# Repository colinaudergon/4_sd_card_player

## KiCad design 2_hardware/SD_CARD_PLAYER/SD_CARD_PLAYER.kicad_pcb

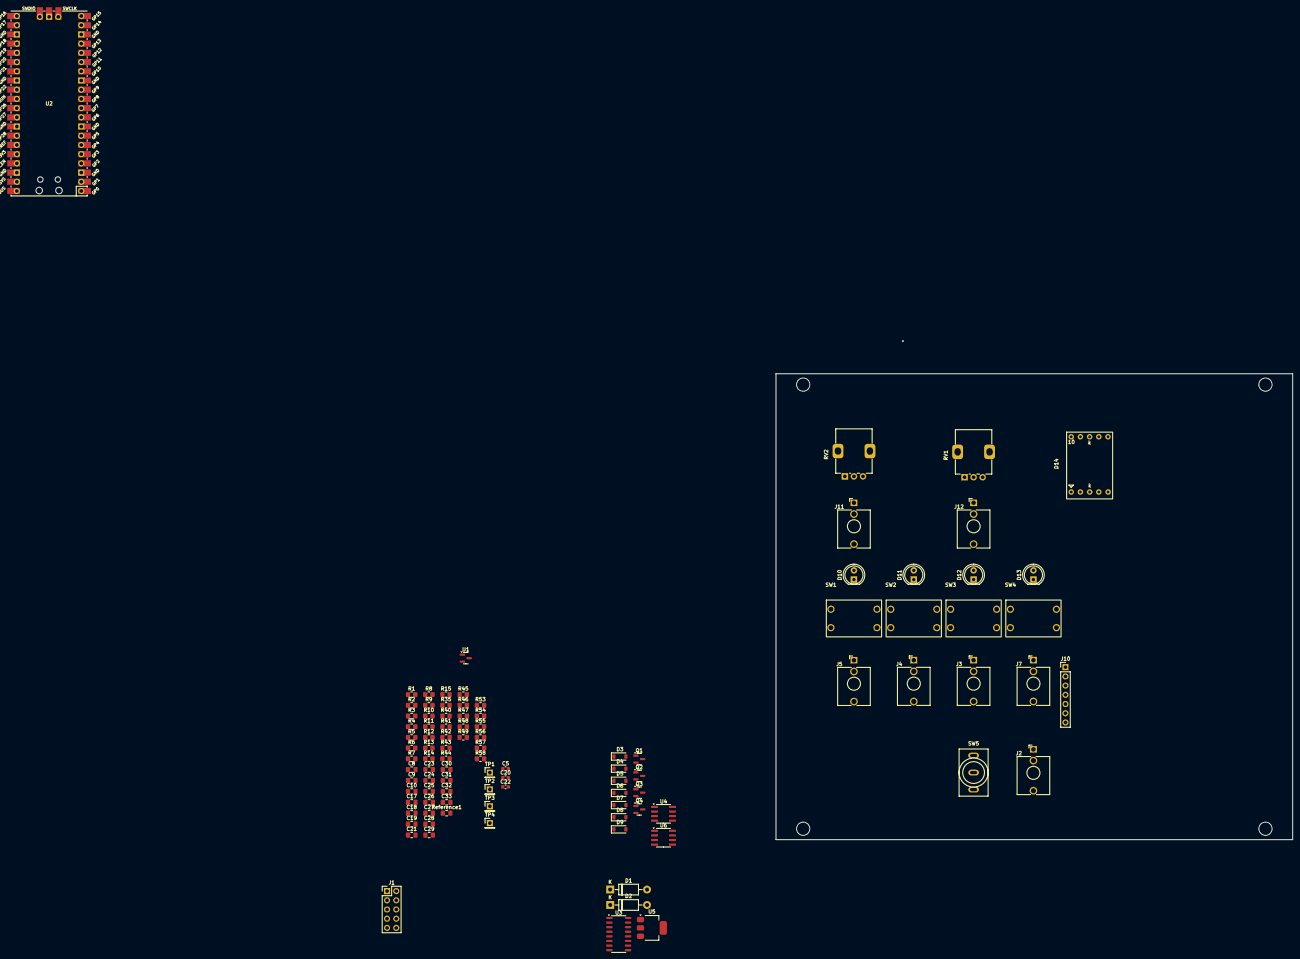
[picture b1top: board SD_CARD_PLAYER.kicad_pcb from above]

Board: 2 copper layers, 142.5 x 128.5 mm, 98 parts (0 on the bottom side), 70 nets, no tracks yet.

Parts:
C5, C20, C22: 10uF; C_0603_1608Metric
C8: 1uF; C_0805_2012Metric_Pad1.18x1.45mm_HandSolder
C9, C10, C17, C18, C19, C21, C24, C25, C30, C32: 100nF; C_0805_2012Metric_Pad1.18x1.45mm_HandSolder
C23, C31, C33: 1nF; C_0805_2012Metric_Pad1.18x1.45mm_HandSolder
C26, C27: 470p; C_0805_2012Metric_Pad1.18x1.45mm_HandSolder
C28, C29: 2.2n; C_0805_2012Metric_Pad1.18x1.45mm_HandSolder
D1, D2: 1N4001; D_DO-41_SOD81_P10.16mm_Horizontal
D3, D4, D7, D8, D9: 1N4148W; D_SOD-123
D5, D6: BAT43W-V; D_SOD-123
D10, D11, D12, D13: LED; LED_D5.0mm
D14: SC_56_11_RT
J1: Conn_02x05_Odd_Even; PinHeader_2x05_P2.54mm_Vertical
J2: audio output; Jack_3.5mm_QingPu_WQP-PJ398SM_Vertical_CircularHoles
J3, J4, J5, J7: Digital Input Jack; Jack_3.5mm_QingPu_WQP-PJ398SM_Vertical_CircularHoles
J10: SD_CARD_CONN; PinHeader_1x07_P2.54mm_Vertical
J11, J12: Analogue Input Jack; Jack_3.5mm_QingPu_WQP-PJ398SM_Vertical_CircularHoles
Q1, Q2, Q3, Q4: MMBT3904; SOT-23
R1, R2, R43, R44: 1K; R_0805_2012Metric_Pad1.20x1.40mm_HandSolder
R3, R7, R9, R35: 100K; R_0805_2012Metric_Pad1.20x1.40mm_HandSolder
R4, R5, R6, R8, R10, R40, R45, R46, R48, R49: 10K; R_0805_2012Metric_Pad1.20x1.40mm_HandSolder
R11, R12, R13, R14, R15: 330; R_0805_2012Metric_Pad1.20x1.40mm_HandSolder
R41, R42, R47: 330R; R_0805_2012Metric_Pad1.20x1.40mm_HandSolder
R53, R57: 200k; R_0805_2012Metric_Pad1.20x1.40mm_HandSolder
R54, R56: 100k; R_0805_2012Metric_Pad1.20x1.40mm_HandSolder
R55, R58: 66.5k; R_0805_2012Metric_Pad1.20x1.40mm_HandSolder
RV1, RV2: 10kB; Potentiometer_Alps_RK09K_Single_Vertical
Reference1: +3.3V; C_0805_2012Metric_Pad1.18x1.45mm_HandSolder
SW1, SW2, SW3, SW4: SW_Push; TSA12110
SW5: SW_SPDT; DIP_SWITCH
TP1: audio_in_ext; PinHeader_1x01_P2.54mm_Vertical
TP2: unused_pin_1; PinHeader_1x01_P2.54mm_Vertical
TP3: unused_pin_2; PinHeader_1x01_P2.54mm_Vertical
TP4: unused_pin_3; PinHeader_1x01_P2.54mm_Vertical
U1: LM4040DBZ-10; SOT-23
U2: PICO_RP2040; RPi_Pico_SMD_TH
U3: 74HC595; SO-16_3.9x9.9mm_P1.27mm
U4: MCP6232; SOIC-8_3.9x4.9mm_P1.27mm
U5: LM1117MP-5.0; SOT-223-3_TabPin2
U6: MCP6002-xMS; SOIC-8_3.9x4.9mm_P1.27mm

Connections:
-Vref: C30.1, RV1.1, RV2.1, U1.2 (A)
AUDIO_PWM: R49.1, U2.1 (GP0)
BANK_CV: C33.2, R58.2, U2.31 (GP26), U6.7
BTN_1: C9.1, R1.1, R5.1, U2.4 (GP2)
BTN_2: C10.1, R2.1, R6.1, U2.5 (GP3)
BTN_3: C18.1, R43.1, R45.1, U2.6 (GP4)
BTN_4: C19.1, R44.1, R46.1, U2.7 (GP5)
EXT_TRIG_1: Q1.3 (C), R40.2, U2.9 (GP6)
EXT_TRIG_2: Q3.3 (C), R8.2, U2.10 (GP7)
EXT_TRIG_3: Q2.3 (C), R4.2, U2.11 (GP8)
EXT_TRIG_4: Q4.3 (C), R10.2, U2.12 (GP9)
GND: C5.2, C8.2, C9.2, C10.2, C17.2, C18.2, C19.2, C20.2, C21.2, C22.2, C23.2, C24.2, C26.1, C27.1, C30.2, C32.2, D3.2 (A), D4.2 (A), D6.2 (A), D8.2 (A), D9.2 (A), D10.1 (K), D11.1 (K), D12.1 (K), D13.1 (K), J1.3, J1.4, J1.5, J1.6, J1.7, J1.8, J2.S, J3.S, J4.S, J5.S, J7.S, J10.3, J10.6, J11.S, J12.S, Q1.2 (E), Q2.2 (E), Q3.2 (E), Q4.2 (E), R15.2, R47.1, RV1.3, RV2.3, SW1.1, SW2.1, SW3.1, SW4.1, SW5.2 (B), U1.1 (K), U2.3 (GND), U2.8 (GND), U2.13 (GND), U2.18 (GND), U2.23 (GND), U2.28 (GND), U2.33 (GND), U2.38 (GND), U3.8 (GND), U3.13 (~OE), U4.4 (V-), U4.5 (+), U5.1 (GND), U6.3 (+), U6.4 (V-), U6.5 (+)
LED_1: R11.1, U2.14 (GP10)
LED_2: R12.1, U2.15 (GP11)
LED_3: R13.1, U2.16 (GP12)
LED_4: R14.1, U2.17 (GP13)
unnamed: C25.1, R41.2
unnamed: C25.2, J2.T
unnamed: C27.2, C28.2, R48.1, R49.2
unnamed: D1.2 (A), J1.1, J1.2
unnamed: D2.2 (A), J1.9, J1.10
unnamed: D3.1 (K), Q1.1 (B), R35.2
unnamed: D4.1 (K), Q2.1 (B), R3.2
unnamed: D5.2 (A), D6.1 (K), R41.1, R42.2, U4.1
unnamed: D7.1 (K), U2.39 (VSYS)
unnamed: D8.1 (K), Q3.1 (B), R7.2
unnamed: D9.1 (K), Q4.1 (B), R9.2
unnamed: D10.2 (A), R11.2
unnamed: D11.2 (A), R12.2
unnamed: D12.2 (A), R13.2
unnamed: D13.2 (A), R14.2
unnamed: D14.3 (k), R15.1
unnamed: J3.T, R3.1
unnamed: J4.T, R7.1
unnamed: J5.T, R9.1
unnamed: J7.T, R35.1
unnamed: J11.T, R54.1
unnamed: J12.T, R56.1
unnamed: R44.2, SW4.3
unnamed: R53.1, RV1.2
unnamed: R57.1, RV2.2
unnamed: R1.2, SW1.3 (2)
unnamed: R2.2, SW2.3 (2)
unnamed: R43.2, SW3.3 (2)
unnamed: C28.1, C29.1, SW5.1 (A)
unnamed: TP2.1, U2.2 (GP1)
unnamed: TP3.1, U2.19 (GP14)
unnamed: TP4.1, U2.20 (GP15)
unnamed: TP1.1, U2.34 (GP28)
unnamed: C26.2, C29.2, R48.2, U4.3 (+)
unnamed: R42.1, R47.2, U4.2 (-)
unnamed: U4.6 (-), U4.7
unnamed: C31.1, R53.2, R54.2, R55.1, U6.2 (-)
unnamed: C33.1, R56.2, R57.2, R58.1, U6.6 (-)
PITCH_CV: C31.2, R55.2, U2.32 (GP27), U6.1
sd_card_SPI0_CS: J10.1, U2.22 (GP17)
sd_card_SPI0_MISO: J10.7, U2.21 (GP16)
sd_card_SPI0_MOSI: J10.2, U2.25 (GP19)
sd_card_SPI0_SCK: J10.5, U2.24 (GP18)
seg_a: D14.7 (a), U3.15 (QA)
seg_b: D14.6 (b), U3.1 (QB)
seg_c: D14.4 (c), U3.2 (QC)
seg_d: D14.2 (d), U3.3 (QD)
seg_e: D14.1 (e), U3.4 (QE)
seg_f: D14.9 (f), U3.5 (QF)
seg_g: D14.10 (g), U3.6 (QG)
shift_clk: U2.29 (GP22), U3.11 (SRCLK)
shift_data: U2.26 (GP20), U3.14 (SER)
shift_latch: U2.27 (GP21), U3.12 (RCLK)
~: C5.1, C8.1, C17.1, C20.1, C21.1, C22.1, C23.1, C24.1, C32.1, D1.1 (K), D5.1 (K), D7.2 (A), J10.4, R4.1, R5.2, R6.2, R8.1, R10.1, R40.1, R45.2, R46.2, Reference1.1, U2.36 (3V3), U3.10 (~SRCLR), U3.16 (VCC), U4.8 (V+), U5.2 (VO), U5.3 (VI), U6.8 (V+)

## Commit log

2024-05-28 Corrected -vref supply schematic, assigned correct footprint to lm4040B10
2024-05-30 Added IBom
2024-06-01 updated schematic
2024-06-01 Update pico_sdCard
2024-06-01 Update test pcb
2024-08-11 SDcardplayerV2 pushed
